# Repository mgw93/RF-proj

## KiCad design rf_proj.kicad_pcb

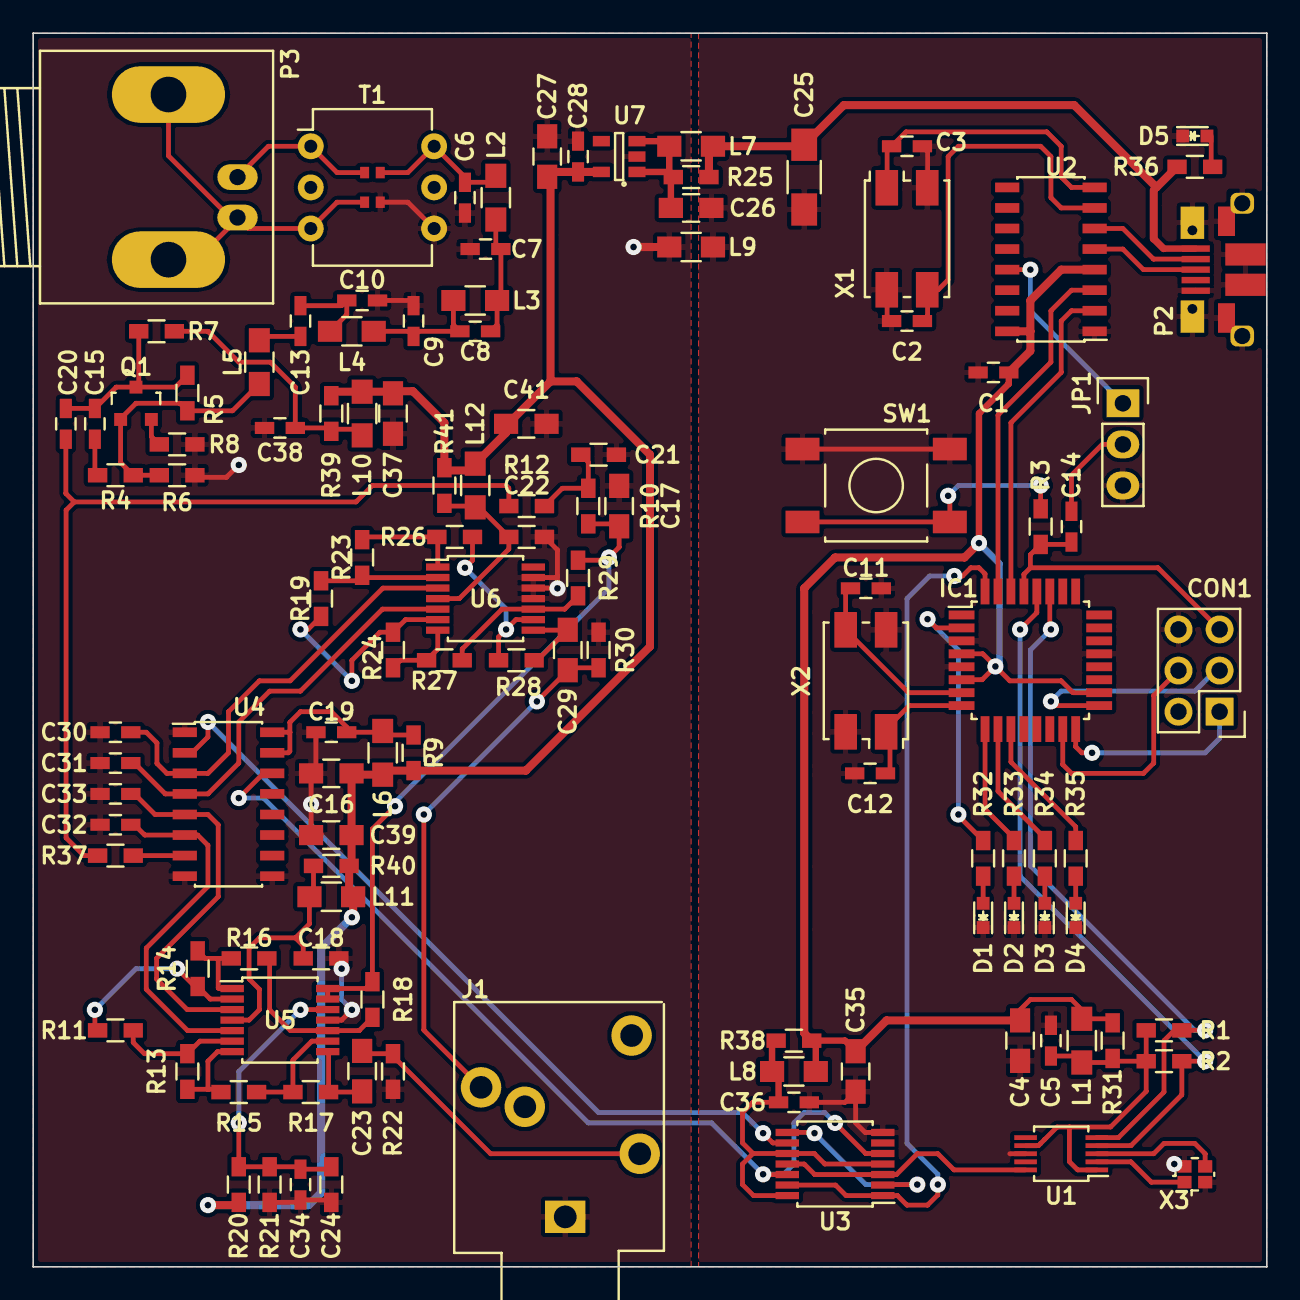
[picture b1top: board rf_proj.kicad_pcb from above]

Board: 2 copper layers, 76.2 x 76.2 mm, 117 parts (0 on the bottom side), 81 nets.

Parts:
C1, C5, C14, C19, C28, C36, C38: 0.1uF; C_0603_HandSoldering
C2, C3, C8, C11, C12: 22pF; C_0603_HandSoldering
C4, C16, C17, C23, C26, C27, C29, C35, C37, C39, C41: 10uF; C_0805_HandSoldering
C6, C10: 390pF; C_0603_HandSoldering
C7, C9: 680pF; C_0603_HandSoldering
C13, C15, C20: 100nF; C_0603_HandSoldering
C18, C21, C22, C24: 0.1uF; R_0603_HandSoldering
C25: 100uF; C_1206_HandSoldering
C30, C31, C32, C33: C_Small; C_0603_HandSoldering
C34: 10uF; C_0603_HandSoldering
CON1: AVR-ISP-6; Pin_Header_Straight_2x03
D1, D2, D3, D4, D5: Led_Small; LED_0603
IC1: ATMEGA328P-A; TQFP-32_7x7mm_Pitch0.8mm
J1: EBS_35
JP1: JUMPER3; Pin_Header_Straight_1x03
L1, L6, L7, L8, L9, L10, L11, L12: INDUCTOR; L_0805_HandSoldering
L2, L3, L4: 1uH; L_0805_HandSoldering
L5: 150nH; L_0805_HandSoldering
P2: USB_OTG; USB_Micro-B
P3: BNC; BNC_Socket_TYCO-AMP_LargePads
Q1: BC849; SOT-23
R1, R2: 1k; R_0603_HandSoldering
R3, R9, R11, R19, R25, R31, R38, R39, R40, R41: R; R_0603_HandSoldering
R4: 330; R_0603_HandSoldering
R5: 6.8k; R_0603_HandSoldering
R6, R20, R21: 10k; R_0603_HandSoldering
R7, R10: 100; R_0603_HandSoldering
R8: 12; R_0603_HandSoldering
R12, R22, R30: 100k; R_0603_HandSoldering
R13, R14, R23, R24: 3.3k; R_0603_HandSoldering
R15, R16, R17, R18, R26, R27, R28, R29: 5.6k; R_0603_HandSoldering
R32, R33, R34, R35, R36: 470; R_0603_HandSoldering
R37: 390; R_0603_HandSoldering
SW1: SW_PUSH; TASTER_9315
T1: TRANSFO; RF-ProjTransformer
U1: Si5351A_3; MSOP-10_3x3mm_Pitch0.5mm
U2: CH340; SOIC-16_3.9x9.9mm_Pitch1.27mm
U3: 74AC74; TSSOP-14_4.4x5mm_Pitch0.65mm
U4: 74CBTLV3253; SOIC-16_3.9x9.9mm_Pitch1.27mm
U5, U6: TLV2464; TSSOP-14_4.4x5mm_Pitch0.65mm
U7: MIC5504-3.3; SOT-23-5
X1: 12MHz; Crystal_SMD_7050_4Pads
X2: 16MHz; Crystal_SMD_7050_4Pads
X3: 25MHz; Crystal_SMD_2016_4Pads

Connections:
+3V3: C1.1, C4.1, C35.1, IC1.4, IC1.6, IC1.18, L1.2, L8.2, R31.1, R38.1, U2.4, U2.16
/3.3A: C16.1, C27.1, C28.1, C37.1, C39.1, C41.1, L6.2, L10.2, L11.2, L12.2, R9.2, R20.2, R39.2, R40.2, R41.2, U7.5
/CLK: U1.10, U3.3, U3.11
/CLK_RST: IC1.32, U3.1, U3.13
/D+: P2.3, U2.5
/D-: P2.2, U2.6
/DTR: JP1.1, U2.13
/IN_A: C32.1, U4.6, U5.5
/IN_B: C33.1, U4.5, U5.3
/IN_C: C30.1, U4.3, U6.3
/IN_D: C31.1, U4.4, U6.5
/OUT_I: C23.2, J1.3, R22.2
/OUT_Q: C29.2, J1.2, R30.2
/RESET: C14.1, CON1.5, IC1.29, R3.1
/RXD: IC1.31, U2.3
/S0: U3.5, U3.12, U4.14
/S1: U3.9, U4.2
/SCL: IC1.28, R2.1, U1.4
/SDA: IC1.27, R1.1, U1.5
/S_Mixer: C20.1, R12.2, R37.2
/TXD: IC1.30, U2.2
/V_REF: C17.1, R10.2, R18.1, R29.1, U5.13, U5.14
/XTAL1: C11.1, IC1.7, X2.2
/XTAL2: C12.1, IC1.8, X2.1
GND: C1.2, C2.2, C3.2, C4.2, C5.2, C11.2, C12.2, C25.2, C26.2, C35.2, C36.2, CON1.6, D1.1, D2.1, D3.1, D4.1, D5.1, IC1.3, IC1.5, IC1.21, JP1.3, L9.2, P2.5, P2.6, SW1.1, U1.8, U2.1, U3.7, X1.3, X2.3, X3.3
GNDA: C6.2, C7.2, C9.2, C10.2, C16.2, C17.2, C18.2, C19.2, C21.2, C22.2, C24.2, C27.2, C28.2, C30.2, C31.2, C32.2, C33.2, C34.2, C37.2, C38.2, C39.2, C41.2, J1.1, L9.1, R6.2, R8.2, R21.1, R22.1, R30.1, T1.3, U4.1, U4.8, U4.9, U5.11, U6.11, U6.12, U6.13, U7.2
unnamed: C2.1, U2.7, X1.2
unnamed: C3.1, U2.8, X1.1
unnamed: C5.1, L1.1, R1.2, R2.2, R31.2, U1.1, U1.7
unnamed: C6.1, L2.2, T1.4
unnamed: C7.1, C8.2, L2.1, L3.2
unnamed: C8.1, C9.1, L3.1, L4.2
unnamed: C10.1, C13.2, L4.1
unnamed: C13.1, L5.2
unnamed: C14.2, JP1.2
unnamed: C15.1, C20.2, Q1.3, R5.1, R7.2
unnamed: C15.2, R4.1
unnamed: C18.1, L11.1, R40.1, U5.4
unnamed: C19.1, L6.1, R9.1, U4.15, U4.16
unnamed: C21.1, R10.1, R12.1
unnamed: C22.1, L12.1, R41.1, U6.4
unnamed: C23.1, R17.1, U5.8
unnamed: C24.1, C34.1, R20.1, R21.2, U5.12
unnamed: C25.1, L7.2, P2.1, R25.2, R36.2
unnamed: C26.1, L7.1, R25.1, U7.1, U7.3
unnamed: C29.1, R28.1, U6.8
unnamed: C38.1, L10.1, R7.1, R39.1
unnamed: CON1.1, IC1.16
unnamed: CON1.3, IC1.17
unnamed: CON1.4, IC1.15
unnamed: D1.2, R32.1
unnamed: D2.2, R33.1
unnamed: D3.2, R34.1
unnamed: D4.2, R35.1
unnamed: D5.2, R36.1
unnamed: IC1.2, R32.2
unnamed: IC1.9, R33.2
unnamed: IC1.10, R34.2
unnamed: IC1.11, R35.2
unnamed: L5.1, Q1.1, R4.2, R5.2, R6.1
unnamed: P3.1, T1.1
unnamed: P3.2, T1.2
unnamed: Q1.2, R8.1
unnamed: R3.2, SW1.2
unnamed: R11.1, R14.2, U5.2
unnamed: R11.2, R13.2, U5.6
unnamed: R13.1, R15.2, U5.7
unnamed: R14.1, R16.2, U5.1
unnamed: R15.1, R17.2, U5.9
unnamed: R16.1, R18.2, U5.10
unnamed: R19.1, R24.2, U6.6
unnamed: R19.2, R23.2, U6.2
unnamed: R23.1, R26.2, U6.1
unnamed: R24.1, R27.2, U6.7
unnamed: R26.1, R28.2, U6.9
unnamed: R27.1, R29.2, U6.10
unnamed: R37.1, U4.7
unnamed: U1.2, X3.1
unnamed: U1.3, X3.2
unnamed: U3.2, U3.8
VCC: C36.1, L8.1, R38.2, U3.4, U3.10, U3.14

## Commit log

2016-06-23 Stand nach Treffen vom 23.06.2016
2016-06-28 Layout verbessert.
2016-07-12 Routing und Fehlerkorrekturen im Schaltplan
2016-07-13 Footprint-Bibliothek hinzugefuegt
2016-07-13 Taster-Footprint angepasst
2016-07-14 Footprints angepasst und Layout bearbeitet
2016-07-14 Layout fertig
2016-07-17 Diverse Layout-Korrekturen und -Verbesserungen
2016-07-18 Weitere Fehlerkorrekturen
